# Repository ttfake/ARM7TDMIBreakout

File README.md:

# ARM7TDMIBreakout
This breakout board is for the ADuC7060 Microcontroller. The core is an ARM7TDMI. This board hasn't been tested yet.

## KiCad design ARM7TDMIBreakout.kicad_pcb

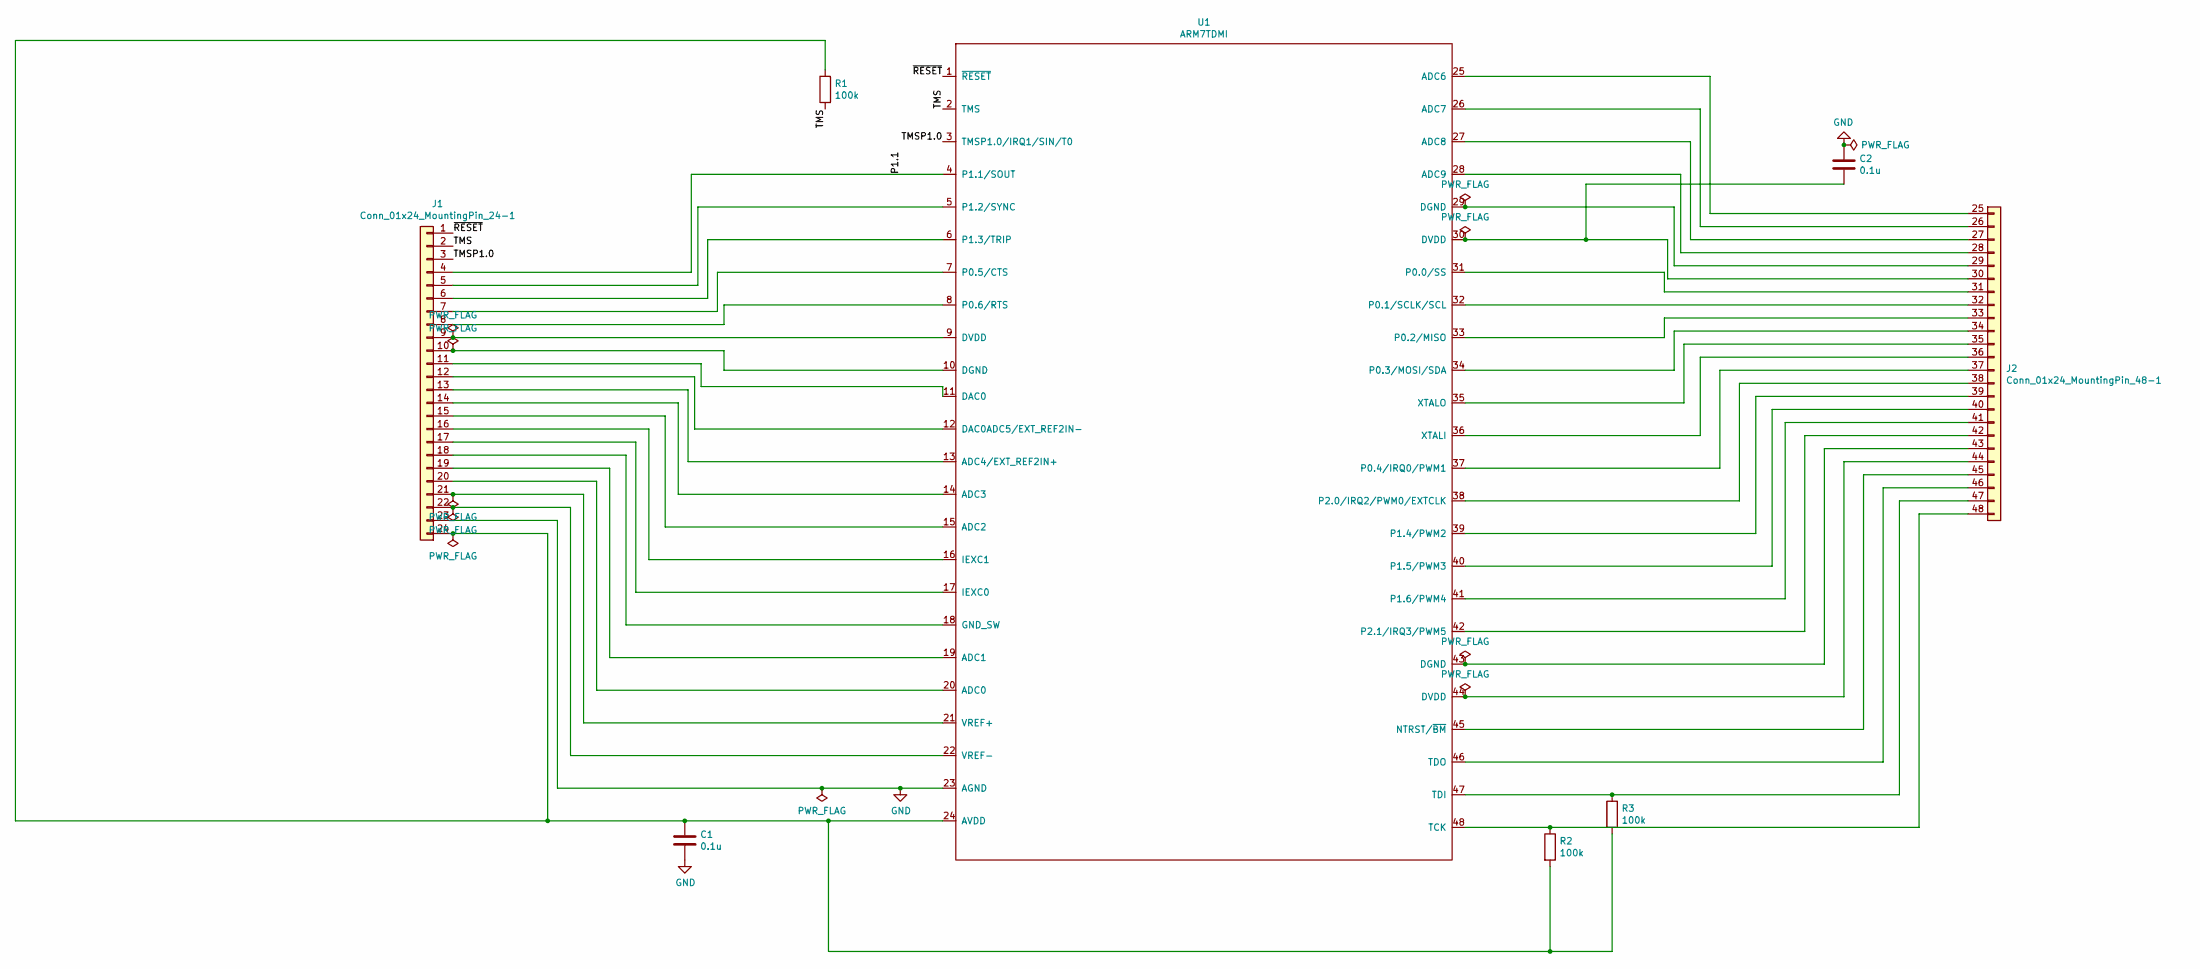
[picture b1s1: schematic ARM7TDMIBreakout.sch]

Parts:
C1, C2: 0.1u; C_0603_HandSoldering
J1: Conn_01x24_MountingPin_24-1; PinHeader_1x24_P2.54mm_Horizontal_1-24
J2: Conn_01x24_MountingPin_48-1; PinHeader_1x24_P2.54mm_Horizontal_25-48
R1, R2, R3: 100k; R_0603_HandSoldering
U1: ARM7TDMI; LQFP-48_7x7mm_P0.5mm

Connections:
/P1.1: J1.4, U1.4 (P1.1/SOUT)
/TMS: J1.2, R1.2, U1.2 (TMS)
/TMSP1.0: J1.3, U1.3 (TMSP1.0/IRQ1/SIN/T0)
/~RESET: J1.1, U1.1 (~RESET)
GND: C1.2, C2.1, J1.23, U1.23 (AGND)
unnamed: C1.1, J1.24, R1.1, R2.2, R3.2, U1.24 (AVDD)
unnamed: C2.2, J2.30, U1.30 (DVDD)
unnamed: J1.5, U1.5 (P1.2/SYNC)
unnamed: J1.6, U1.6 (P1.3/TRIP)
unnamed: J1.7, U1.7 (P0.5/CTS)
unnamed: J1.8, U1.8 (P0.6/RTS)
unnamed: J1.9, U1.9 (DVDD)
unnamed: J1.10, U1.10 (DGND)
unnamed: J1.11, U1.11 (DAC0)
unnamed: J1.12, U1.12 (DAC0ADC5/EXT_REF2IN−)
unnamed: J1.13, U1.13 (ADC4/EXT_REF2IN+)
unnamed: J1.14, U1.14 (ADC3)
unnamed: J1.15, U1.15 (ADC2)
unnamed: J1.16, U1.16 (IEXC1)
unnamed: J1.17, U1.17 (IEXC0)
unnamed: J1.18, U1.18 (GND_SW)
unnamed: J1.19, U1.19 (ADC1)
unnamed: J1.20, U1.20 (ADC0)
unnamed: J1.21, U1.21 (VREF+)
unnamed: J1.22, U1.22 (VREF-)
unnamed: J2.25, U1.25 (ADC6)
unnamed: J2.26, U1.26 (ADC7)
unnamed: J2.27, U1.27 (ADC8)
unnamed: J2.28, U1.28 (ADC9)
unnamed: J2.29, U1.29 (DGND)
unnamed: J2.31, U1.31 (P0.0/SS)
unnamed: J2.32, U1.32 (P0.1/SCLK/SCL)
unnamed: J2.33, U1.33 (P0.2/MISO)
unnamed: J2.34, U1.34 (P0.3/MOSI/SDA)
unnamed: J2.35, U1.35 (XTALO)
unnamed: J2.36, U1.36 (XTALI)
unnamed: J2.37, U1.37 (P0.4/IRQ0/PWM1)
unnamed: J2.38, U1.38 (P2.0/IRQ2/PWM0/EXTCLK)
unnamed: J2.39, U1.39 (P1.4/PWM2)
unnamed: J2.40, U1.40 (P1.5/PWM3)
unnamed: J2.41, U1.41 (P1.6/PWM4)
unnamed: J2.42, U1.42 (P2.1/IRQ3/PWM5)
unnamed: J2.43, U1.43 (DGND)
unnamed: J2.44, U1.44 (DVDD)
unnamed: J2.45, U1.45 (NTRST/~BM)
unnamed: J2.46, U1.46 (TDO)
unnamed: J2.47, R3.1, U1.47 (TDI)
unnamed: J2.48, R2.1, U1.48 (TCK)

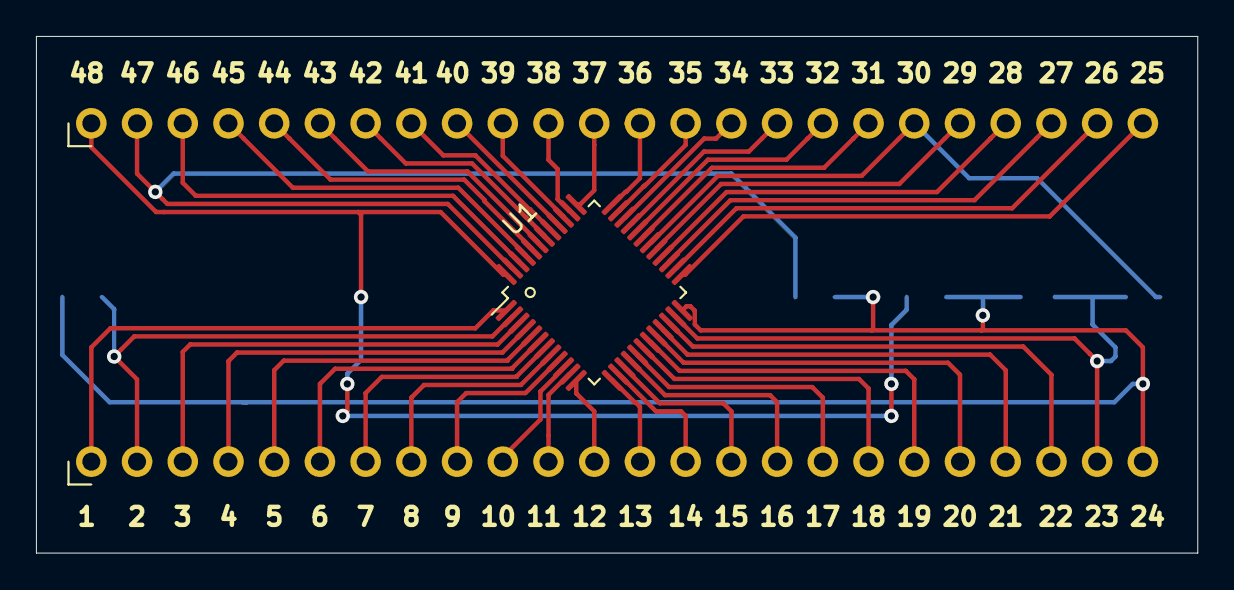
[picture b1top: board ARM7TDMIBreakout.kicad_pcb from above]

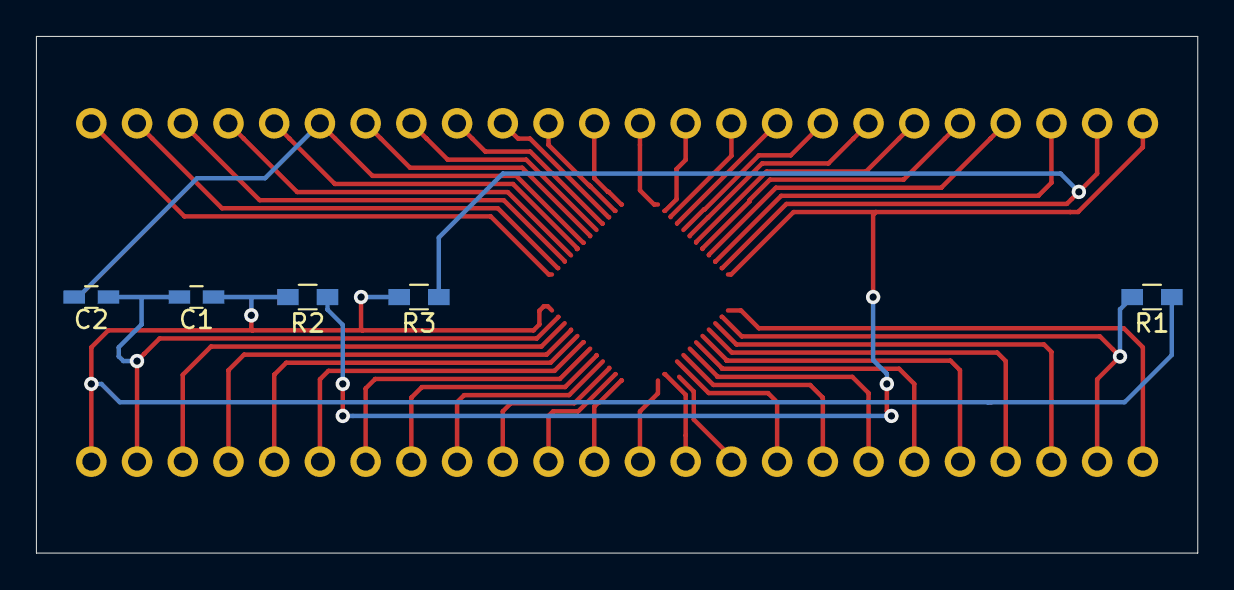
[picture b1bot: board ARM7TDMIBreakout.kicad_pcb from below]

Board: 2 copper layers, 64.5 x 28.7 mm, 8 parts (5 on the bottom side), 48 nets.

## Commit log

2019-11-13 ARM7TDMIBreakout Board for the ADuC7060 Mictrocontroller
2019-11-15 Fixed: Connected bypass capacitors to AGND
